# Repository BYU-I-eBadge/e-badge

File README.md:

# eBadge

**eBadge** is a customizable, hackable electronics badge designed for students to explore, build, and learn throughout their academic journey. It’s more than just a badge—it's a personal electronics lab, wearable project canvas, and long-term learning tool.

## Features

- Custom PCB with microcontroller 
- Modular peripherals: LEDs, sensors, buttons, displays, etc.
- Fully programmable with open-source firmware
- Designed for learning — from blinking LEDs to building full apps
- Battery-powered & portable — perfect for hacking on the go

## What’s in This Repo?

```bash
e-badge/
├── docs/           # Project documentation, setup guides, and images
├── hardware/       # Schematics, PCB layouts, BOMs, and 3D models
├── firmware/       # Embedded code for the badge's microcontroller
├── software/       # Host-side apps, test tools, or configurators
├── assets/         # Logos, badge graphics, and artwork
├── test/           # Scripts for testing hardware and firmware
├── LICENSE-CODE
├── LICENSE-HARDWARE
├── LICENSE-DOCS
├── README.md
└── .gitignore
```
## License

- **Hardware** – [CERN-OHL-S v2.0](./LICENSE-HARDWARE)
- **Firmware/Code** – [MIT License](./LICENSE-CODE)
- **Docs & Assets** – [CC BY-SA 4.0](./LICENSE-DOCS)

## Contributors

- Nathan Jack (jackn@byui.edu)
- Lynn Watson (lynn@lswatson.com)
- Jason Allred (allredjas@byui.edu)
- Richard Grimmett (grimmettr@byui.edu)
- Carl Gibbons (gibbonsc@byui.edu)
- Craig Lindstrom (lindstromc@byui.edu)
- Gary Godderidge (godderidgeg@byui.edu)
- Matt Manley (manleym@byui.edu)

# TODO (Senior project, delete when done)
- Fix screen connector
	- Use LCSC part C11086

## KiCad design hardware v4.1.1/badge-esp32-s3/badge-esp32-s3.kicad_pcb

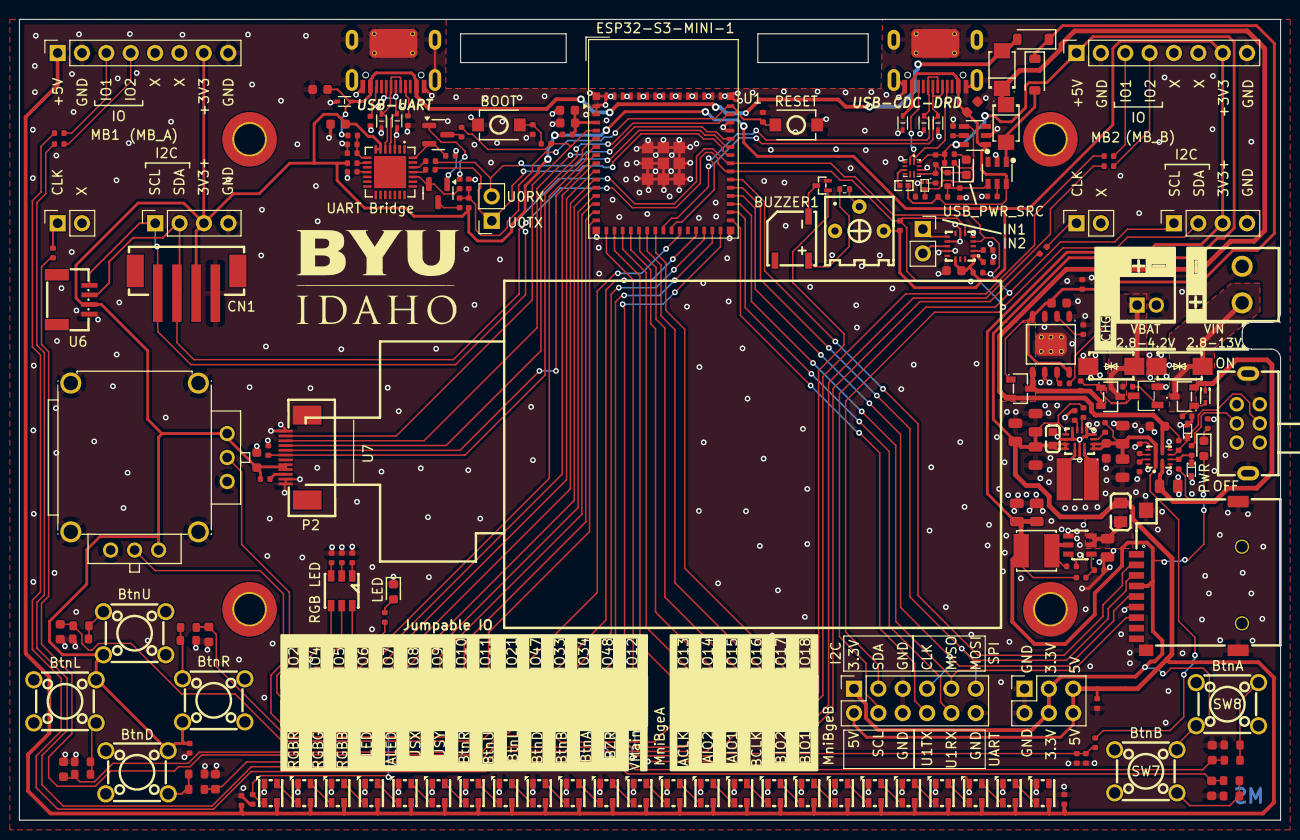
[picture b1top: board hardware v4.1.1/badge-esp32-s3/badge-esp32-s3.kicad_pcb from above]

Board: 2 copper layers, 131.5 x 83.5 mm, 215 parts (0 on the bottom side), 167 nets.

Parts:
AL1, AL2, AL3, AL4, AL5, AL6, AL7, AL8, AL9, AL10, AL11, AL12, AL13, AL14, AL15, AL16, AL17, AL18, AL19, AL20, AL21, AL22, AL23, AL24: SK6805MICRO-J; LED-SMD_4P-SK6805MICRO-J
BUZZER1: MLT-5020; BUZ-SMD_L5.0-W5.5-P4.60
C1, C5, C6, C7, C12, C24, C39: 10uF; C_0603
C2, C14: 100nF; C_0603
C3, C4, C10, C11, C25, C34, C35, C36, C41, C44: 100nF; C_0402
C8, C9, C15, C16, C32, C33: 1uF; C_0402
C18, C19, C20, C21, C22, C23: 1uF; C_0603
C26: 4.7uF; C_0603
C28, C29, C30, C31, C38, C40: 22uF; C_0805
C37: TMK107BBJ106MA-T; C0603
C42, C43, C45: 10uF; C_0805
CN1: B4B-PH-SM4-TB (LF)(SN); CONN-SMD_B4B-PH-SM4-TB-LF-SN
Card1: TF PUSH; TF-SMD_TF-PUSH
D1, D14, D19: Red; D_0603
D2, D3, D4, D6, D7, D8: LESD5D5.0CT1G; SOD-523_L1.2-W0.8-LS1.6-BI
D5, D16: B0520W; D_SOD-123
D9: SMAJ5.0CA_C116601; SMA_L4.3-W2.7-LS5.1-BI
D10: B5819WT; D_SOD-523
D11: MM5Z9V1T1G; SOD-523_L1.2-W0.8-LS1.6-RD-1
D12: Green; D_0805
D13: SMAJ13CA; SMA_L4.3-W2.7-LS5.1-BI
D15, D20: MM5Z5V1T1G; SOD-523F_L1.2-W0.8-LS1.7-RD
D17, D18: SS32F_C719168; SMAF_L3.5-W2.6-LS4.7-RD
H1, H2, H3, H4: MountingHole; MountingHole_3.2mm_M3_ISO7380_Pad_TopBottom
J1, J2: Connector, USB-TYPE-C-16P; TYPE-C-SMD_HX-TYPE-C-16PIN
J3, J9: Conn_02x06_Odd_Even; PinSocket_2x06_P2.54mm_Vertical
J4: Conn_02x15_Odd_Even; PinSocket_2x15_P2.54mm_Vertical
J5, J12, J14, J15: Conn_01x02_Socket; PinSocket_1x02_P2.54mm_Vertical
J6, J13: Conn_01x04_Socket; PinSocket_1x04_P2.54mm_Vertical
J7, J8: Conn_01x08_Socket; PinSocket_1x08_P2.54mm_Vertical
J11: Conn_02x03_Odd_Even; PinSocket_2x03_P2.54mm_Vertical
L1: ANR4030T3R9M; IND-SMD_L4.0-W4.0
L2: MPZ2012S101AT000; L0805
L4: FTC404020S1R5MGCA; IND-SMD_L4.1-W4.1_SPM40XX
LED1: RS-3535MWAM; LED-ARRAY-SMD_L3.7-W3.5-P1.10-TL
MB1, MB2: MiniBadge_Full; MiniBadge_Full_NoEdges
P1: PH-2A_C2319; CONN-TH_2P-P2.00_PH-2A_C2319
P2: FPC 0.5MM 12P Pull type H2.0mm Pick up; FPC-SMD_12P-L11.5-W5.4-P0.50
P3: WJ124-3.81-2P; CONN-TH_2P-P3.81_KF124-3.81-2P
Q1, Q2: SS8050 200-350; Q_SOT-23
Q3: AP1606; DFN-3L_L1.0-W0.6-P0.65-BR
Q5: DTC114E; DTC114EE
Q7, Q8, Q9: AO3415_C54938718; SOT-23-3_L2.9-W1.3-P1.90-LS2.4-BR
Q10: DMN3150L-7; SOT-23-3_L2.9-W1.6-P1.90-LS2.8-BR-CW
R1, R11, R12, R64: 0Ω; R_0402
R2: 3362P-1-501_C48997906; RES-ADJ-TH_3362P
R3, R4: 5.1kΩ; R_0402
R5: 910k; R0402
R6, R10, R13, R14, R17, R44, R46, R48, R66, R68, R69, R70: 10kΩ; R_0402
R7: 22kΩ; R_0402
R8: 47kΩ; R_0402
R9, R25: 1kΩ; R_0402
R15, R16, R55: 470Ω; R_0402
R18, R20, R40, R47, R49, R50, R51, R52: 100Ω; R_0402
R19: 24kΩ; R_0402
R21, R24: 47Ω; R_0402
R22, R54: 300Ω; R_0402
R23: YF16-FL7.2-B5KA(45-10)-R-A28; JOYTICK-TH_YF16-DFL7.2-B5KO-45-10-B5KO-55--RG-A22
R26: 2.2kΩ; R_0402
R27, R28, R29, R30, R31, R32, R33, R34, R35, R36, R37, R38: 10kΩ; R_0603
R39, R53, R56, R60, R62: 100kΩ; R_0402
R41: 150kΩ; R_0402
R42: 27Ω; R_0402_1005Metric
R43, R45: 4.7kΩ; R_0402
R58, R61: 3.3kΩ; R_0402
R59, R71: 1MΩ; R_0402
R63: 39kΩ; R_0402
R65: 12kΩ; R_0402
R67: 68kΩ; R_0402
SW1, SW2: TS-1088-AR02016; SW-SMD_L3.9-W3.0-P4.45
SW4, SW5, SW6, SW7, SW8, SW9: TS665CJ; SW-TH_4P-L6.0-W6.0-P4.50-LS6.5
SW10: SK22D02G5; SW-TH_SK22D02G5
U1: ESP32-S3-MINI-1-N4R2; ESP32-S2-MINI-1
U2: TPS630701RNMR; VQFN-HR-15_L3.0-W2.5-P0.50-BL_TPS63070RNMR
U3: CP2102N-A02-GQFN28R; QFN-28_L5.0-W5.0-P0.50-TL-EP3.3
U4: TP4056; ESOP-8_L4.9-W3.9-P1.27-LS6.0-BL-EP
U5: TPS2121RUXR; VQFN-HR-12_L2.5-W2.0-P0.50-BL
U6: ZX-SH1.0-4PWT; CONN-SMD_4P-P1.00_MEGASTAR_ZX-SH1.0-4PWT
U7: HS20HS072RX-fpc; OLED-SMD_HS20HS072RX-pins_removed
U8: TUSB321AIRWBR; X2QFN-12_L1.6-W1.6-P0.40-BL
U9: AP63203WU-7; TSOT-26_L2.9-W1.6-P0.95-LS2.8-BL
U11, U12: SY6288F1ABC; SOT-23-6_L2.9-W1.6-P0.95-LS2.8-BL
U18: MMA8452QR1_C11360; QFN-16_L3.0-W3.0-P0.50-TL_MMA8452QR1

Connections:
+3.3V: C7.1, C10.1, C14.1, C16.1, C26.2, C28.1, C29.1, CN1.3, Card1.4 (VDD), D1.2, J3.1, J6.3, J7.7, J8.7, J11.3, J11.4, J13.3, L1.2, P2.8 (IOVCC), P2.9 (VCC), R1.2, R2.3, R9.2, R17.1, R18.1, R23.3, R23.4, R43.1, R45.1, R64.1, SW4.2 (B), SW5.2 (B), SW6.2 (B), SW7.2 (B), SW8.2 (B), SW9.2 (B), U3.6 (VDD), U3.7 (VREGIN), U6.3, U18.1 (VDDIO), U18.14 (VDD)
/5V_stable: AL1.4 (VDD), AL2.4 (VDD), AL3.4 (VDD), AL4.4 (VDD), AL5.4 (VDD), AL6.4 (VDD), AL7.4 (VDD), AL8.4 (VDD), AL9.4 (VDD), AL10.4 (VDD), AL11.4 (VDD), AL12.4 (VDD), AL13.4 (VDD), AL14.4 (VDD), AL15.4 (VDD), AL16.4 (VDD), AL17.4 (VDD), AL18.4 (VDD), AL19.4 (VDD), AL20.4 (VDD), AL21.4 (VDD), AL22.4 (VDD), AL23.4 (VDD), AL24.4 (VDD), C15.1, C30.1, C31.1, C32.1, C33.1, C37.2, C40.1, J3.2, J7.1, J8.1, J11.5, J11.6, L2.1, R6.1, R53.1, R58.1, R69.1, U2.5 (FB), U2.7 (VOUT), U2.8 (VOUT), U8.12 (VDD), U12.6 (IN)
/AButtonMid: C22.1, J4.26, R36.2
/AddrLedMid: AL1.3 (DIN), J4.10, R68.1
/BButtonMid: C21.1, J4.24, R34.2
/BatteryVoltage: C34.1, J4.30, R41.2, R44.1
/BuzzerMid: J4.28, Q5.1 (B)
/DownButtonMid: C23.1, J4.22, R38.2
/ESP USB/CC1: J2.A5 (CC1), U8.1 (CC1)
/ESP USB/CC2: J2.B5 (CC2), U8.2 (CC2)
/ESP USB/USB_ID: D10.1, D19.1, R6.2, R66.1, U8.9 (ID)
/ESP USB/USB_SINK_EN: C3.1, D10.2, R70.2, U11.4 (EN/ENB)
/ESP USB/USB_SOURCE_EN: C4.1, Q3.3 (D), R69.2, U12.4 (EN/ENB)
/ESP USB/VBUS: C6.1, D8.2, J2.A9B4 (VBUS), J2.B9A4 (VBUS), R5.1, R70.1, U11.6 (IN), U12.1 (OUT)
/ESP_EN: C9.1, C36.2, R15.2, R17.2, SW2.2, U1.45 (EN)
/ESP_USB+: D6.2, J2.A6 (D+), J2.B6 (D+), U1.24 (USB_D+)
/ESP_USB-: D7.2, J2.A7 (D-), J2.B7 (D-), U1.23 (USB_D-)
/GPIO0: P2.2 (CS), R16.2, R55.2, U1.4 (IO0)
/GPIO1: P2.6 (RST), R39.1, U1.5 (IO1)
/GPIO2: J4.1, U1.6 (IO2)
/GPIO3: P2.5 (SDA), U1.7 (IO3)
/GPIO4: J4.3, U1.8 (IO4)
/GPIO5: J4.5, U1.9 (IO5)
/GPIO6: J4.7, U1.10 (IO6)
/GPIO7: J4.9, U1.11 (IO7)
/GPIO8: J4.11, U1.12 (IO8)
/GPIO9: J4.13, U1.13 (IO9)
/GPIO10: J4.15, U1.14 (IO10)
/GPIO11: J4.17, U1.15 (IO11)
/GPIO12: J4.29, U1.16 (IO12)
/GPIO13: J9.1, U1.17 (IO13)
/GPIO14: J9.3, U1.18 (IO14)
/GPIO15: J9.5, U1.19 (IO15)
/GPIO16: J9.7, U1.20 (IO16)
/GPIO17: J9.9, U1.21 (IO17)
/GPIO18: J9.11, U1.22 (IO18)
/GPIO21: J4.19, U1.25 (IO21)
/GPIO33: J4.23, U1.28 (IO33)
/GPIO34: J4.25, U1.29 (IO34)
/GPIO35: J3.8, U1.31 (IO35)
/GPIO36: J3.10, U1.32 (IO36)
/GPIO37: Card1.7 (DAT0), J3.9, U1.33 (IO37)
/GPIO38: Card1.5 (CLX), J3.7, U1.34 (IO38)
/GPIO39: Card1.3 (CMD), J3.11, U1.35 (IO39)
/GPIO40: Card1.2 (CD/DAT3), U1.36 (IO40)
/GPIO41: CN1.2, J3.3, J6.2, J13.2, R45.2, U1.37 (IO41), U6.2, U18.6 (SDA)
/GPIO42: CN1.1, J3.4, J6.1, J13.1, R43.2, U1.38 (IO42), U6.1, U18.4 (SCL)
/GPIO45: P2.3 (RS), U1.41 (IO45)
/GPIO46: P2.4 (SCL), U1.44 (IO46)
/GPIO47: J4.21, U1.27 (IO47)
/GPIO48: J4.27, U1.30 (IO48)
/JoystickXMid: J4.12, R23.2
/JoystickYMid: J4.14, R23.5
/LEDSingleMid: J4.8, R22.1
/LEDs/AL8_OUT: AL8.1 (DOUT), AL9.3 (DIN)
/LEDs/AL16_OUT: AL16.1 (DOUT), AL17.3 (DIN)
/LeftButtonMid: C18.1, J4.20, R28.2
/Onboard Peripheral/Accelormeter/INT 1 (output to MCU, NN): J15.2, U18.11 (INT1)
/Onboard Peripheral/Accelormeter/INT 2 (output to MCU, NN): J15.1, U18.9 (INT2)
/Power Input Managment/BATT_RAW: D9.2, P1.1, Q7.3 (D), R62.1
/Power Input Managment/OV1_EN_N: D20.1 (K), R71.2, SW10.2, U5.5 (OV1)
/Power Input Managment/OV2_EN_N: R67.2, SW10.5
/Power Input Managment/VIN: C42.1, D11.1 (K), Q8.2 (S), R59.1, U5.2 (IN2)
/Power Input Managment/VIN_RAW: D13.2, P3.1, Q8.3 (D)
/RGBBlueMid: J4.6, LED1.6 (+)
/RGBGreenMid: J4.4, LED1.5 (+)
/RGBRedMid: J4.2, LED1.4 (+)
/RightButtonMid: C20.1, J4.16, R32.2
/U0RX: J14.2, R11.2, U1.40 (RXD0)
/U0TX: J14.1, R12.2, U1.39 (TXD0)
/UART Interface/USB_DN: D3.2, J1.A7 (D-), J1.B7 (D-), U3.5 (D-)
/UART Interface/USB_DP: D2.2, J1.A6 (D+), J1.B6 (D+), U3.4 (D+)
/USB_HC: C24.1, D17.1 (K), D18.1 (K), Q9.2 (S), R71.1, U5.7 (IN1)
/USB_LC: C12.1, D5.1, D12.2, D16.1, Q9.1 (G), R56.1, U4.4 (VCC), U4.8 (CE)
/UpButtonMid: C19.1, J4.18, R30.2
/VBATT: Q7.2 (S), Q9.3 (D), R60.1, U4.5 (BAT)
/VBUS: C5.1, D4.2, D5.2, D17.2 (A), J1.A9B4 (VBUS), J1.B9A4 (VBUS), R7.1
/Voltage Management/SW: C44.2, L1.1, U9.5 (SW)
/Voltage Management/VIN: C38.1, L2.2, U9.2 (EN), U9.3 (VIN)
/minibadge/MB1CLK: J9.2, R49.2
/minibadge/MB1IO1: J9.6, R40.1
/minibadge/MB1IO2: J9.4, R47.1
/minibadge/MB2CLK: J9.8, R52.2
/minibadge/MB2IO1: J9.12, R50.1
/minibadge/MB2IO2: J9.10, R51.1
GND: AL1.2 (VSS), AL2.2 (VSS), AL3.2 (VSS), AL4.2 (VSS), AL5.2 (VSS), AL6.2 (VSS), AL7.2 (VSS), AL8.2 (VSS), AL9.2 (VSS), AL10.2 (VSS), AL11.2 (VSS), AL12.2 (VSS), AL13.2 (VSS), AL14.2 (VSS), AL15.2 (VSS), AL16.2 (VSS), AL17.2 (VSS), AL18.2 (VSS), AL19.2 (VSS), AL20.2 (VSS), AL21.2 (VSS), AL22.2 (VSS), AL23.2 (VSS), AL24.2 (VSS), C1.2, C2.2, C3.2, C4.2, C5.2, C6.2, C7.2, C8.2, C9.2, C10.2, C11.2, C12.2, C14.2, C15.2, C16.2, C18.2, C19.2, C20.2, C21.2, C22.2, C23.2, C24.2, C25.2, C26.1, C28.2, C29.2, C30.2, C31.2, C32.2, C33.2, C34.2, C35.1, C36.1, C37.1, C38.2, C39.2, C40.2, C41.2, C42.2, C43.2, C45.2, CN1.4, Card1.6 (VSS), Card1.10, Card1.11, Card1.12, Card1.13, D2.1, D3.1, D4.1, D6.1, D7.1, D8.1, D9.1, D13.1, D14.1, D15.2 (A), D20.2 (A), J1.A12B1 (GND), J1.B12A1 (GND), J1.S1 (SHIELD), J2.A12B1 (GND), J2.B12A1 (GND), J2.S1 (SHIELD), J3.5, J3.6, J3.12, J6.4, J7.2, J7.8, J8.2, J8.8, J11.1, J11.2, J13.4, P1.2, P2.1 (GND), P2.11 (K), P2.12 (GND), P3.2, Q3.2 (S), Q5.2 (E), Q10.3 (S), R3.2, R4.2, R8.2, R10.2, R19.2, R20.2, R21.2, R23.1, R23.6, R23.7 (shell), R23.8 (shell), R23.9 (shell), R23.10 (shell), R24.2, R26.2, R27.2, R29.2, R31.2, R33.2, R35.2, R37.2, R39.2, R44.2, R48.2, R54.1, R56.2, R61.2, R63.2, R65.2, R68.2, SW1.1, SW2.1, SW10.3, SW10.4, SW10.7, SW10.8, U1.1 (GND), U1.2 (GND), U1.42 (GND), U1.43 (GND), U1.46 (GND), U1.47 (GND), U1.48 (GND), U1.49 (GND), U1.50 (GND), U1.51 (GND), U1.52 (GND), U1.53 (GND), U1.54 (GND), U1.55 (GND), U1.56 (GND), U1.57 (GND), U1.58 (GND), U1.59 (GND), U1.60 (GND), U1.61 (GND), U1.62 (GND), U1.63 (GND), U1.64 (GND), U1.65 (GND), U2.1 (PS/SYNC), U2.4 (GND), U2.6 (FB2), U2.10 (PGND), U2.15 (VSEL), U3.3 (GND), U4.1 (TEMP), U4.3 (GND), U4.6 (STDBY#), U4.9 (EP), U5.3 (CP2), U5.6 (PR1), U5.9 (ST), U5.12 (GND), U6.4, U8.3 (CURRENT_MODE), U8.10 (GND), U9.4 (GND), U11.2 (GND), U12.2 (GND), U18.5 (GND), U18.7 (SA0), U18.10 (GND), U18.12 (GND)
unnamed: AL1.1 (DOUT), AL2.3 (DIN)
unnamed: AL2.1 (DOUT), AL3.3 (DIN)
unnamed: AL3.1 (DOUT), AL4.3 (DIN)
unnamed: AL4.1 (DOUT), AL5.3 (DIN)
unnamed: AL5.1 (DOUT), AL6.3 (DIN)
unnamed: AL6.1 (DOUT), AL7.3 (DIN)
unnamed: AL7.1 (DOUT), AL8.3 (DIN)
unnamed: AL9.1 (DOUT), AL10.3 (DIN)
unnamed: AL10.1 (DOUT), AL11.3 (DIN)
unnamed: AL11.1 (DOUT), AL12.3 (DIN)
unnamed: AL12.1 (DOUT), AL13.3 (DIN)
unnamed: AL13.1 (DOUT), AL14.3 (DIN)
unnamed: AL14.1 (DOUT), AL15.3 (DIN)
unnamed: AL15.1 (DOUT), AL16.3 (DIN)
unnamed: AL17.1 (DOUT), AL18.3 (DIN)
unnamed: AL18.1 (DOUT), AL19.3 (DIN)
unnamed: AL19.1 (DOUT), AL20.3 (DIN)
unnamed: AL20.1 (DOUT), AL21.3 (DIN)
unnamed: AL21.1 (DOUT), AL22.3 (DIN)
unnamed: AL22.1 (DOUT), AL23.3 (DIN)
unnamed: AL23.1 (DOUT), AL24.3 (DIN)
unnamed: BUZZER1.1 (+), R42.2
unnamed: BUZZER1.2 (-), Q5.3 (C)
unnamed: C35.2, R55.1, SW1.2
unnamed: D1.1, R54.2
unnamed: D11.2 (A), Q8.1 (G), R48.1
unnamed: D12.1, R25.1
unnamed: D14.2, R22.2
unnamed: D15.1 (K), R59.2, R67.1, U5.4 (OV2)
unnamed: D16.2, D18.2 (A), U11.1 (OUT)
unnamed: D19.2, R58.2
unnamed: J1.A5 (CC1), R3.1
unnamed: J1.B5 (CC2), R4.1
unnamed: J5.1, R49.1
unnamed: J7.3, R40.2
unnamed: J7.4, R47.2
unnamed: J8.3, R50.2
unnamed: J8.4, R51.2
unnamed: J12.1, R52.1
unnamed: LED1.1 (-), R21.1
unnamed: LED1.2 (-), R24.1
unnamed: LED1.3 (-), R20.1
unnamed: P2.10 (A), R18.2
unnamed: Q1.1 (B), R13.2
unnamed: Q1.3 (C), R15.1
unnamed: Q1.2 (E), R14.1, U3.24 (RTS)
unnamed: Q2.1 (B), R14.2
unnamed: Q2.3 (C), R16.1
unnamed: Q2.2 (E), R13.1, U3.28 (DTR)
unnamed: Q3.1 (G), R66.2
unnamed: Q7.1 (G), Q10.2 (D), R60.2
unnamed: Q10.1 (G), R62.2
unnamed: R2.2, R42.1
unnamed: R27.1, R28.1, SW4.4 (D)
unnamed: R29.1, R30.1, SW5.4 (D)
unnamed: R31.1, R32.1, SW6.4 (D)
unnamed: R33.1, R34.1, SW7.4 (D)
unnamed: R35.1, R36.1, SW8.3 (C)
unnamed: R37.1, R38.1, SW9.4 (D)
unnamed: C1.1, C2.1, R1.1, U1.3 (3V3)
unnamed: R46.2, U2.14 (EN)
unnamed: L4.1, U2.11 (L1)
unnamed: L4.2, U2.9 (L2)
unnamed: R53.2, U2.2 (PG)
unnamed: C25.1, U2.3 (VAUX)
unnamed: R9.1, U3.9 (RSTb)
unnamed: R12.1, U3.25 (RXD)
unnamed: R10.1, U3.11 (SUSPENDb)
unnamed: R11.1, U3.26 (TXD)
unnamed: C8.1, R7.2, R8.1, U3.8 (VBUS)
unnamed: R25.2, U4.7 (CHRG#)
unnamed: R26.1, U4.2 (PROG)
unnamed: R63.1, U5.10 (ILM)
unnamed: C41.1, U5.11 (SS)
unnamed: R5.2, U8.5 (VBUS_DET)
unnamed: C44.1, U9.6 (BST)
unnamed: R19.1, R64.2, U9.1 (FB)
unnamed: R61.1, U11.5 (ISET)
unnamed: R65.1, U12.5 (ISET)
unnamed: C11.1, U18.2 (BYP)
PWR_RAW: C39.1, C43.1, C45.1, R41.1, R46.1, U2.12 (VIN), U2.13 (VIN), U5.1 (OUT), U5.8 (OUT)

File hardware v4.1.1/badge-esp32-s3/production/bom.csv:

Designator,Footprint,Quantity,Value,LCSC Part #
"AL1, AL10, AL11, AL12, AL13, AL14, AL15, AL16, AL17, AL18, AL19, AL2, AL20, AL21, AL22, AL23, AL24, AL3, AL4, AL5, AL6, AL7, AL8, AL9",LED-SMD_4P-SK6805MICRO-J,24,SK6805MICRO-J,C2909056
BUZZER1,BUZ-SMD_L5.0-W5.5-P4.60,1,MLT-5020,C94598
"C1, C12, C24, C39, C5, C6, C7",C_0603,7,10uF,C96446
"C10, C11, C25, C3, C35, C36, C4",C_0402,7,100nF,C1525
"C14, C2",C_0603,2,100nF,C14663
"C15, C16, C32, C33, C8, C9",C_0402,6,1uF,C52923
"C18, C19, C20, C21, C22, C23",C_0603,6,1uF,C15849
C26,C_0603,1,4.7uF,C19666
"C28, C29, C30, C31, C38, C40",C_0805,6,22uF,C296720
"C34, C41, C44",C_0402,3,100nF,C307331
C37,C0603,1,TMK107BBJ106MA-T,C386081
"C42, C43, C45",C_0805,3,10uF,C440198
CARD1,TF-SMD_TF-PUSH,1,TF PUSH,C393941
CN1,CONN-SMD_B4B-PH-SM4-TB-LF-SN,1,B4B-PH-SM4-TB (LF)(SN),C160354
"D1, D14, D19",D_0603,3,Red,C2286
D10,D_SOD-523,1,B5819WT,C7502714
D11,SOD-523_L1.2-W0.8-LS1.6-RD-1,1,MM5Z9V1T1G,C242268
D12,D_0805,1,Green,C2297
D13,SMA_L4.3-W2.7-LS5.1-BI,1,SMAJ13CA,C19077534
"D15, D20",SOD-523F_L1.2-W0.8-LS1.7-RD,2,MM5Z5V1T1G,C146754
"D16, D5",D_SOD-123,2,B0520W,C7502707
"D17, D18",SMAF_L3.5-W2.6-LS4.7-RD,2,SS32F_C719168,C719168
"D2, D3, D4, D6, D7, D8",SOD-523_L1.2-W0.8-LS1.6-BI,6,LESD5D5.0CT1G,C5199850
D9,SMA_L4.3-W2.7-LS5.1-BI,1,SMAJ5.0CA_C116601,C116601
"J1, J2",TYPE-C-SMD_HX-TYPE-C-16PIN,2,"Connector, USB-TYPE-C-16P",C2927039
J11,PinSocket_2x03_P2.54mm_Vertical,1,Conn_02x03_Odd_Even,C541853
"J12, J14, J15, J5",PinSocket_1x02_P2.54mm_Vertical,4,Conn_01x02_Socket,C7499322
"J13, J6",PinSocket_1x04_P2.54mm_Vertical,2,Conn_01x04_Socket,C2718488
"J3, J9",PinSocket_2x06_P2.54mm_Vertical,2,Conn_02x06_Odd_Even,C5307342
J4,PinSocket_2x15_P2.54mm_Vertical,1,Conn_02x15_Odd_Even,C7499350
"J7, J8",PinSocket_1x08_P2.54mm_Vertical,2,Conn_01x08_Socket,C42385698
L1,IND-SMD_L4.0-W4.0,1,ANR4030T3R9M,C6808101
L2,L0805,1,MPZ2012S101AT000,C15957
L4,IND-SMD_L4.1-W4.1_SPM40XX,1,FTC404020S1R5MGCA,C39676069
LED1,LED-ARRAY-SMD_L3.7-W3.5-P1.10-TL,1,RS-3535MWAM,C842778
P1,CONN-TH_2P-P2.00_PH-2A_C2319,1,PH-2A_C2319,C2319
P2,FPC-SMD_12P-L11.5-W5.4-P0.50,1,FPC 0.5MM 12P Pull type H2.0mm Pick up,C11086
P3,CONN-TH_2P-P3.81_KF124-3.81-2P,1,WJ124-3.81-2P,C69811
"Q1, Q2",Q_SOT-23,2,SS8050 200-350,C2150
Q10,SOT-23-3_L2.9-W1.6-P1.90-LS2.8-BR-CW,1,DMN3150L-7,C156268
Q3,DFN-3L_L1.0-W0.6-P0.65-BR,1,AP1606,C2849580
Q5,DTC114EE,1,DTC114E,C94400
"Q7, Q8, Q9",SOT-23-3_L2.9-W1.3-P1.90-LS2.4-BR,3,AO3415_C54938718,C54938718
"R1, R11, R12, R64",R_0402,4,0Ω,C17168
"R10, R13, R14, R17, R44, R46, R48, R6, R66, R68, R69, R70",R_0402,12,10kΩ,C25744
"R15, R16, R55",R_0402,3,470Ω,C25117
"R18, R20, R40, R47, R49, R50, R51, R52",R_0402,8,100Ω,C25076
R2,RES-ADJ-TH_3362P,1,3362P-1-501_C48997906,C48997906
"R21, R24",R_0402,2,47Ω,C25118
"R22, R54",R_0402,2,300Ω,C25102
R23,JOYTICK-TH_YF16-DFL7.2-B5KO-45-10-B5KO-55--RG-A22,1,YF16-FL7.2-B5KA(45-10)-R-A28,C37323739
"R25, R9",R_0402,2,1kΩ,C11702
R26,R_0402,1,2.2kΩ,C25879
"R27, R28, R29, R30, R31, R32, R33, R34, R35, R36, R37, R38",R_0603,12,10kΩ,C25804
"R3, R4",R_0402,2,5.1kΩ,C25905
"R39, R53, R56, R60, R62",R_0402,5,100kΩ,C25741
R41,R_0402,1,150kΩ,C25755
R42,0402,1,27Ω,
"R43, R45",R_0402,2,4.7kΩ,C25900
R5,R0402,1,910k,C2909391
"R58, R61",R_0402,2,3.3kΩ,C25890
"R59, R71",R_0402,2,1MΩ,C26083
R63,R_0402,1,39kΩ,C25783
R65,R_0402,1,12kΩ,C25752
R67,R_0402,1,68kΩ,C36871
R7,R_0402,1,22kΩ,C25768
R8,R_0402,1,47kΩ,C25792
"SW1, SW2",SW-SMD_L3.9-W3.0-P4.45,2,TS-1088-AR02016,C720477
SW10,SW-TH_SK22D02G5,1,SK22D02G5,C22435630
"SW4, SW5, SW6, SW7, SW8, SW9",SW-TH_4P-L6.0-W6.0-P4.50-LS6.5,6,TS665CJ,C393938
U1,ESP32-S2-MINI-1,1,ESP32-S3-MINI-1-N4R2,C3013941
"U11, U12",SOT-23-6_L2.9-W1.6-P0.95-LS2.8-BL,2,SY6288F1ABC,C2875458
U18,QFN-16_L3.0-W3.0-P0.50-TL_MMA8452QR1,1,MMA8452QR1_C11360,C11360
U2,VQFN-HR-15_L3.0-W2.5-P0.50-BL_TPS63070RNMR,1,TPS630701RNMR,C2876599
U3,QFN-28_L5.0-W5.0-P0.50-TL-EP3.3,1,CP2102N-A02-GQFN28R,C964632
U4,ESOP-8_L4.9-W3.9-P1.27-LS6.0-BL-EP,1,TP4056,C16581
U5,VQFN-HR-12_L2.5-W2.0-P0.50-BL,1,TPS2121RUXR,C485916
U6,CONN-SMD_4P-P1.00_MEGASTAR_ZX-SH1.0-4PWT,1,ZX-SH1.0-4PWT,C7430446
U8,X2QFN-12_L1.6-W1.6-P0.40-BL,1,TUSB321AIRWBR,C2674046
U9,TSOT-26_L2.9-W1.6-P0.95-LS2.8-BL,1,AP63203WU-7,C780769

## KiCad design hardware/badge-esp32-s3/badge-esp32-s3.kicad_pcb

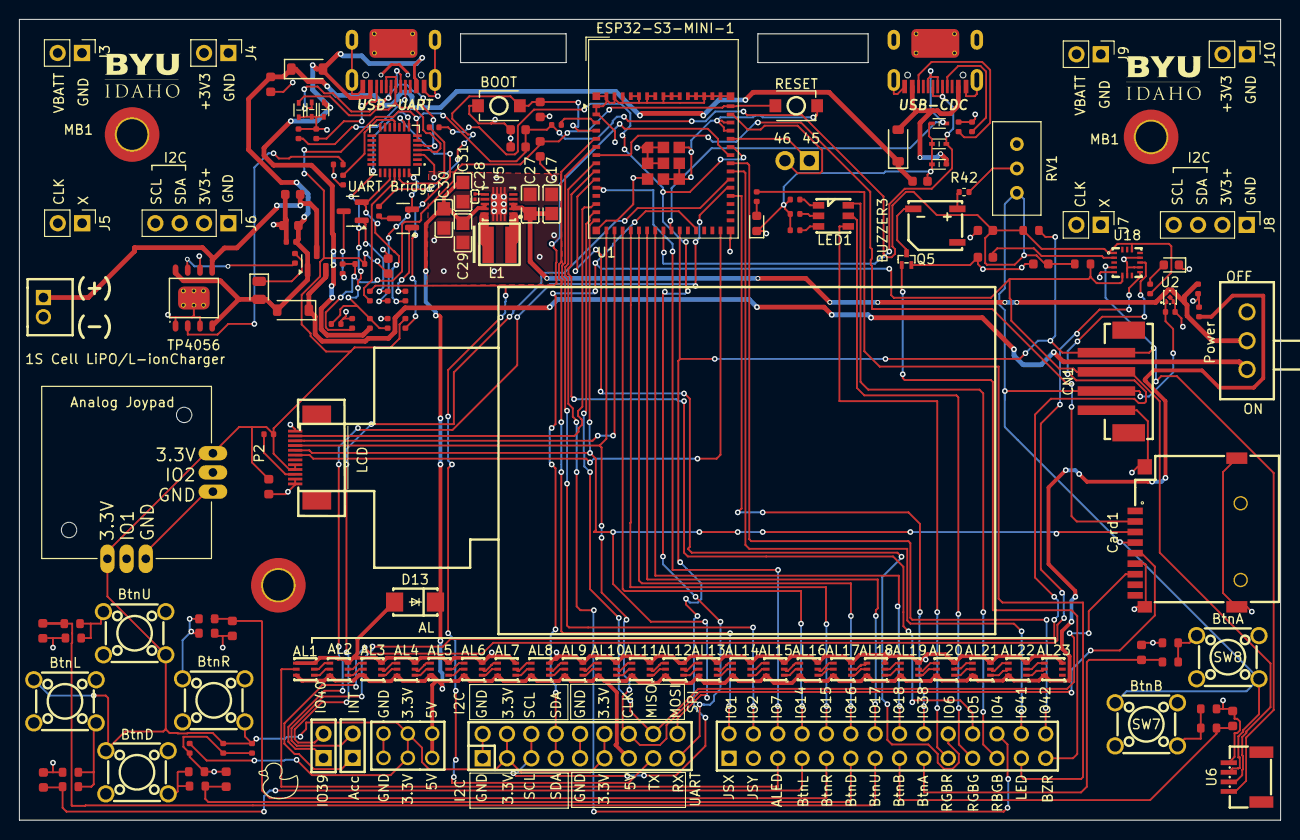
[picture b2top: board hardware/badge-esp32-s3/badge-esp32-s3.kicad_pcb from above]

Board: 2 copper layers, 131.5 x 83.5 mm, 157 parts (0 on the bottom side), 140 nets.

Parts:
AL1, AL2, AL3, AL4, AL5, AL6, AL7, AL8, AL9, AL10, AL11, AL12, AL13, AL14, AL15, AL16, AL17, AL18, AL19, AL20, AL21, AL22, AL23: LED-SMD_6P-L2.2-W2.2-TL-1
BUZZER3: MLT-5020; BUZ-SMD_L5.0-W5.5-P4.60
C1, C5, C6, C7, C12, C13: 10uF; C_0603
C2, C10, C11, C14, C24, C25: 100nF; C_0603
C3, C4, C8, C9, C15, C15#2, C16, C17: 1uF; C_0402
C17#2, C27: 10uF; C0805
C18, C19, C20, C21, C22, C23: 1uF; C_0603
C26: 4.7uF; C_0603
C28: 100nF; C0201
C29, C30, C31: 22uF; C0805
CN1: B4B-PH-SM4-TB (LF)(SN); CONN-SMD_B4B-PH-SM4-TB-LF-SN
CN2: HDR-TH_2P-P2.54-V-F
CN3: HDR-TH_2P-P2.54-V-F
Card1: TF PUSH; TF-SMD_TF-PUSH
D1, D10: Red; D_0603
D2, D3, D4, D6, D7, D8: LESD5D5.0CT1G; SOD-523_L1.2-W0.8-LS1.6-BI
D5, D9, D11: B0520W; D_SOD-123
D12: Green; D_0805
D13: SMAJ7.0A; SMA_L4.5-W2.6-LS5.1-RD
H2: HDR-TH_18P-P2.54-V-F-R2-C9-S2.54-1
J1, J2: Connector, USB-TYPE-C-16P; TYPE-C-SMD_HX-TYPE-C-16PIN
J3, J4, J5, J7, J9, J10: Conn_01x02_Socket; PinHeader_1x02_P2.54mm_Vertical
J6, J8: Conn_01x04_Socket; PinHeader_1x04_P2.54mm_Vertical
L1: 1uH; IND-SMD_L4.0-W4.0_XFL4020-102MEB
LCD: OLED-SMD_HS20HS072RX
LED1: RS-3535MWAM; LED-ARRAY-SMD_L3.7-W3.5-P1.10-TL
MB1, MB1#2: MiniBadge_Full; MiniBadge_Full_NoEdges
P1: PH-2A_C2319; CONN-TH_2P-P2.00_PH-2A_C2319
P2: FPC 0.5MM 12P Pull type H2.0mm Pick up; FPC-SMD_12P-L11.5-W5.4-P0.50
Power1: SK-12F04-G050; SW-TH_G-SWITCH_SK-12F04-G050
Q1, Q2: SS8050 200-350; Q_SOT-23
Q3: HL2301A; Q_SOT-23
Q5: DTC114E; SOT-523_L1.6-W0.8-P1.00-BR
R1, R11, R12, R15, R16: 0Ω; R_0402
R2, R3, R4, R5, R6, R19: 5.1kΩ; R_0402
R7: 22kΩ; R_0402
R8: 47kΩ; R_0402
R9, R25: 1kΩ; R_0402
R10, R13, R14, R17: 10kΩ; R_0402
R18, R20: 100Ω; R_0402
R21, R22: 47Ω; R_0402
R24: 100kΩ; R_0402
R26: 2.2kΩ; R_0402
R27, R28, R29, R30, R31, R32, R33, R34, R35, R36, R37, R38: 10kΩ; R_0603
R39, R40: 4.7kΩ; R_0603
R42: 27Ω; R_0402_1005Metric
RV1: 1000Ω; Potentiometer_Bourns_3296W_Vertical
S1: 2765; SW_2765
SW1, SW2: TS-1088-AR02016; SW-SMD_L3.9-W3.0-P4.45
SW4, SW5, SW6, SW7, SW8, SW9: TS665CJ; SW-TH_4P-L6.0-W6.0-P4.50-LS6.5
U1: ESP32-S3-MINI-1-N4R2; ESP32-S2-MINI-1
U2: NCP167BMX330TBG; XDFN-4_L1.0-W1.0-P0.65-BL-EP
U3: CP2102N-A02-GQFN28R; QFN-28_L5.0-W5.0-P0.50-TL-EP3.3
U4: TP4056; ESOP-8_L4.9-W3.9-P1.27-LS6.0-BL-EP
U5: TPS63061DSCR; WSON-10_L3.0-W3.0-P0.50-BL-EP-A
U6: ZX-SH1.0-4PWT; CONN-SMD_4P-P1.00_MEGASTAR_ZX-SH1.0-4PWT
U14: CONN-TH_HX-PM2.54-2X3P-ZC
U18: MMA8452QR1_C11360; QFN-16_L3.0-W3.0-P0.50-TL_MMA8452QR1
U19: FH2.54-09-02PZD; HDR-TH_2P-P2.54-V-M-5
U20: 2x14_female; HDR-TH_28P-P2.54-V-F-R2-C14-S2.54

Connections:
+3.3V: C1.1, C2.1, C4.1, C7.1, C14.1, C15#2.1, C16.1, C17.1, C24.2, C26.2, CN1.3, Card1.4 (VDD), H2.3, H2.4, H2.11, H2.12, P2.8 (IOVCC), P2.9 (VCC), R1.1, R2.1, R9.2, R17.1, R18.1, R39.1, R40.1, RV1.1, S1.X-, S1.Y-, SW4.1 (A), SW5.1 (A), SW6.1 (A), SW7.1 (A), SW8.1 (A), SW9.1 (A), U2.1 (OUT), U3.6 (VDD), U3.7 (VREGIN), U6.3, U14.2, U14.5, U18.1 (VDDIO), U18.14 (VDD)
+4V: C3.1, C17#2.2, C27.2, Power1.2, U2.3 (EN), U2.4 (IN), U5.2 (VIN), U5.3 (EN)
/5V_stable: AL1.3 (VDD), AL2.3 (VDD), AL3.3 (VDD), AL4.3 (VDD), AL5.3 (VDD), AL6.3 (VDD), AL7.3 (VDD), AL8.3 (VDD), AL9.3 (VDD), AL10.3 (VDD), AL11.3 (VDD), AL12.3 (VDD), AL13.3 (VDD), AL14.3 (VDD), AL15.3 (VDD), AL16.3 (VDD), AL17.3 (VDD), AL18.3 (VDD), AL19.3 (VDD), AL20.3 (VDD), AL21.3 (VDD), AL22.3 (VDD), AL23.3 (VDD), C15.1, C29.2, C30.2, C31.2, D13.1 (K), H2.13, U5.8 (FB), U5.9 (VOUT), U14.3, U14.4
/AButtonMid: C22.1, R36.2, U20.17
/AddrLedMid: AL1.2 (DI), U20.5
/BButtonMid: C21.1, R34.2, U20.15
/BuzzerMid: Q5.1 (B), U20.27
/Charging/VBATT: C13.1, P1.1, Q3.3 (D), U4.5 (BAT)
/DownButtonMid: C23.1, R38.2, U20.11
/ESP_EN: C9.1, C11.2, R15.2, R17.2, SW2.2, U1.45 (EN)
/ESP_USB+: D6.2, J2.A6 (D+), J2.B6 (D+), U1.24 (USB_D+)
/ESP_USB-: D7.2, J2.A7 (D-), J2.B7 (D-), U1.23 (USB_D-)
/GPIO0: C10.2, R16.2, SW1.2, U1.4 (IO0)
/GPIO1: U1.5 (IO1), U20.2
/GPIO2: U1.6 (IO2), U20.4
/GPIO3: Card1.2 (CD/DAT3), U1.7 (IO3)
/GPIO4: U1.8 (IO4), U20.24
/GPIO5: U1.9 (IO5), U20.22
/GPIO6: U1.10 (IO6), U20.20
/GPIO7: U1.11 (IO7), U20.6
/GPIO9: P2.2 (CS), U1.13 (IO9)
/GPIO10: Card1.7 (DAT0), H2.16, U1.14 (IO10)
/GPIO11: Card1.3 (CMD), H2.18, P2.5 (SDA), U1.15 (IO11)
/GPIO12: Card1.5 (CLX), H2.14, P2.4 (SCL), U1.16 (IO12)
/GPIO13: P2.3 (RS), U1.17 (IO13)
/GPIO14: U1.18 (IO14), U20.8
/GPIO15: U1.19 (IO15), U20.10
/GPIO16: U1.20 (IO16), U20.12
/GPIO17: U1.21 (IO17), U20.14
/GPIO18: U1.22 (IO18), U20.16
/GPIO21: CN1.1, H2.5, H2.6, R39.2, U1.25 (IO21), U6.1, U18.4 (SCL)
/GPIO38: U1.34 (IO38), U20.18
/GPIO39: CN3.1, U1.35 (IO39)
/GPIO40: CN3.2, U1.36 (IO40)
/GPIO41: U1.37 (IO41), U20.26
/GPIO42: U1.38 (IO42), U20.28
/GPIO45: U1.41 (IO45), U19.1
/GPIO46: U1.44 (IO46), U19.2
/GPIO47: CN1.2, H2.7, H2.8, R40.2, U1.27 (IO47), U6.2, U18.6 (SDA)
/GPIO48: P2.6 (RST), U1.30 (IO48)
/LEDSingleMid: R19.1, U20.25
/LEDs/BO_AL9: AL9.5 (BO), AL10.1 (BI)
/LEDs/BO_AL18: AL18.5 (BO), AL19.1 (BI)
/LEDs/DO_AL9: AL9.4 (DO), AL10.2 (DI)
/LEDs/DO_AL18: AL18.4 (DO), AL19.2 (DI)
/LeftButtonMid: C20.1, R32.2, U20.9
/Onboard Peripheral/Accelormeter/INT 1 (output to MCU, NN): CN2.2, U18.11 (INT1)
/Onboard Peripheral/Accelormeter/INT 2 (output to MCU, NN): CN2.1, U18.9 (INT2)
/RGBBlueMid: LED1.6 (+), U20.23
/RGBGreenMid: LED1.5 (+), U20.21
/RGBRedMid: LED1.4 (+), U20.19
/RightButtonMid: C18.1, R28.2, U20.7
/U0RX: H2.17, R11.2, U1.40 (RXD0)
/U0TX: H2.15, R12.2, U1.39 (TXD0)
/UART Interface/USB_DN: D3.2, J1.A7 (D-), J1.B7 (D-), U3.5 (D-)
/UART Interface/USB_DP: D2.2, J1.A6 (D+), J1.B6 (D+), U3.4 (D+)
/USB_5V: C5.1, C6.1, C12.1, D5.1, D9.1, D11.2, D12.2, Q3.1 (G), R24.2, U4.4 (VCC), U4.8 (CE)
/UpButtonMid: C19.1, R30.2, U20.13
/VBUS: D4.2, D5.2, J1.A9B4 (VBUS), J1.B9A4 (VBUS), R7.1
/VBUSB: D8.2, D9.2, J2.A9B4 (VBUS), J2.B9A4 (VBUS)
GND: AL1.1 (BI), AL1.6 (GND), AL2.6 (GND), AL3.6 (GND), AL4.6 (GND), AL5.6 (GND), AL6.6 (GND), AL7.6 (GND), AL8.6 (GND), AL9.6 (GND), AL10.6 (GND), AL11.6 (GND), AL12.6 (GND), AL13.6 (GND), AL14.6 (GND), AL15.6 (GND), AL16.6 (GND), AL17.6 (GND), AL18.6 (GND), AL19.6 (GND), AL20.6 (GND), AL21.6 (GND), AL22.6 (GND), AL23.6 (GND), C1.2, C2.2, C3.2, C4.2, C5.2, C6.2, C7.2, C8.2, C9.2, C10.1, C11.1, C12.2, C13.2, C14.2, C15.2, C15#2.2, C16.2, C17.2, C17#2.1, C18.2, C19.2, C20.2, C21.2, C22.2, C23.2, C24.1, C25.1, C26.1, C27.1, C28.1, C29.1, C30.1, C31.1, CN1.4, Card1.6 (VSS), Card1.10, Card1.11, Card1.12, Card1.13, D1.1, D2.1, D3.1, D4.1, D6.1, D7.1, D8.1, D10.1, D13.2 (A), H2.1, H2.2, H2.9, H2.10, J1.A12B1 (GND), J1.B12A1 (GND), J1.S1 (SHIELD), J2.A12B1 (GND), J2.B12A1 (GND), J2.S1 (SHIELD), P1.2, P2.1 (GND), P2.11 (K), P2.12 (GND), Power1.3, Q5.2 (E), R3.2, R4.2, R5.2, R6.2, R8.2, R10.2, R20.2, R21.2, R22.2, R24.1, R26.2, R27.2, R29.2, R31.2, R33.2, R35.2, R37.2, S1.X+, S1.Y+, SW1.1, SW2.1, U1.1 (GND), U1.2 (GND), U1.42 (GND), U1.43 (GND), U1.46 (GND), U1.47 (GND), U1.48 (GND), U1.49 (GND), U1.50 (GND), U1.51 (GND), U1.52 (GND), U1.53 (GND), U1.54 (GND), U1.55 (GND), U1.56 (GND), U1.57 (GND), U1.58 (GND), U1.59 (GND), U1.60 (GND), U1.61 (GND), U1.62 (GND), U1.63 (GND), U1.64 (GND), U1.65 (GND), U2.2 (GND), U2.5 (EPAD), U3.3 (GND), U4.1 (TEMP), U4.3 (GND), U4.6 (STDBY#), U4.9 (EP), U5.4 (PS/SYNC), U5.7 (GND), U5.11 (PGND), U6.4, U14.1, U14.6, U18.5 (GND), U18.7 (SA0), U18.10 (GND), U18.12 (GND)
unnamed: AL1.5 (BO), AL2.1 (BI)
unnamed: AL1.4 (DO), AL2.2 (DI)
unnamed: AL2.5 (BO), AL3.1 (BI)
unnamed: AL2.4 (DO), AL3.2 (DI)
unnamed: AL3.5 (BO), AL4.1 (BI)
unnamed: AL3.4 (DO), AL4.2 (DI)
unnamed: AL4.5 (BO), AL5.1 (BI)
unnamed: AL4.4 (DO), AL5.2 (DI)
unnamed: AL5.5 (BO), AL6.1 (BI)
unnamed: AL5.4 (DO), AL6.2 (DI)
unnamed: AL6.5 (BO), AL7.1 (BI)
unnamed: AL6.4 (DO), AL7.2 (DI)
unnamed: AL7.5 (BO), AL8.1 (BI)
unnamed: AL7.4 (DO), AL8.2 (DI)
unnamed: AL8.5 (BO), AL9.1 (BI)
unnamed: AL8.4 (DO), AL9.2 (DI)
unnamed: AL10.5 (BO), AL11.1 (BI)
unnamed: AL10.4 (DO), AL11.2 (DI)
unnamed: AL11.5 (BO), AL12.1 (BI)
unnamed: AL11.4 (DO), AL12.2 (DI)
unnamed: AL12.5 (BO), AL13.1 (BI)
unnamed: AL12.4 (DO), AL13.2 (DI)
unnamed: AL13.5 (BO), AL14.1 (BI)
unnamed: AL13.4 (DO), AL14.2 (DI)
unnamed: AL14.5 (BO), AL15.1 (BI)
unnamed: AL14.4 (DO), AL15.2 (DI)
unnamed: AL15.5 (BO), AL16.1 (BI)
unnamed: AL15.4 (DO), AL16.2 (DI)
unnamed: AL16.5 (BO), AL17.1 (BI)
unnamed: AL16.4 (DO), AL17.2 (DI)
unnamed: AL17.5 (BO), AL18.1 (BI)
unnamed: AL17.4 (DO), AL18.2 (DI)
unnamed: AL19.5 (BO), AL20.1 (BI)
unnamed: AL19.4 (DO), AL20.2 (DI)
unnamed: AL20.5 (BO), AL21.1 (BI)
unnamed: AL20.4 (DO), AL21.2 (DI)
unnamed: AL21.5 (BO), AL22.1 (BI)
unnamed: AL21.4 (DO), AL22.2 (DI)
unnamed: AL22.5 (BO), AL23.1 (BI)
unnamed: AL22.4 (DO), AL23.2 (DI)
unnamed: BUZZER3.1 (+), R42.2
unnamed: BUZZER3.2 (-), Q5.3 (C)
unnamed: D1.2, R2.2
unnamed: D10.2, R19.2
unnamed: D12.1, R25.1
unnamed: J1.A5 (CC1), R3.1
unnamed: J1.B5 (CC2), R4.1
unnamed: J2.A5 (CC1), R5.1
unnamed: J2.B5 (CC2), R6.1
unnamed: LED1.1 (-), R21.1
unnamed: LED1.2 (-), R22.1
unnamed: LED1.3 (-), R20.1
unnamed: P2.10 (A), R18.2
unnamed: Q1.1 (B), R13.2
unnamed: Q1.3 (C), R15.1
unnamed: Q1.2 (E), R14.1, U3.24 (RTS)
unnamed: Q2.1 (B), R14.2
unnamed: Q2.3 (C), R16.1
unnamed: Q2.2 (E), R13.1, U3.28 (DTR)
unnamed: D11.1, Power1.1, Q3.2 (S)
unnamed: R42.1, RV1.2
unnamed: R27.1, R28.1, SW4.4 (D)
unnamed: R29.1, R30.1, SW5.4 (D)
unnamed: R31.1, R32.1, SW6.4 (D)
unnamed: R33.1, R34.1, SW7.4 (D)
unnamed: R35.1, R36.1, SW8.4 (D)
unnamed: R37.1, R38.1, SW9.4 (D)
unnamed: R1.2, U1.3 (3V3)
unnamed: R9.1, U3.9 (RSTb)
unnamed: R12.1, U3.25 (RXD)
unnamed: R10.1, U3.11 (SUSPENDb)
unnamed: R11.1, U3.26 (TXD)
unnamed: C8.1, R7.2, R8.1, U3.8 (VBUS)
unnamed: R25.2, U4.7 (CHRG#)
unnamed: R26.1, U4.2 (PROG)
unnamed: L1.1, U5.1 (L1)
unnamed: L1.2, U5.10 (L2)
unnamed: C28.2, U5.6 (VAUX)
unnamed: C25.2, U18.2 (BYP)

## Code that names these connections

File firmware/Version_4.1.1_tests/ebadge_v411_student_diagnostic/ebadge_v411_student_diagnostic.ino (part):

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    3
  );

  printAt(10, 150, "Watch GPIO6 status LED and RGB LED.");
  printAt(10, 168, "Sequence repeats automatically.");
}

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void drawPixelStatus() {
  tft.fillRect(0, 40, 320, 160, ST77XX_BLACK);

  printAt(10, 48, "GPIO7 / 24 SK6805 LEDs", ST77XX_WHITE, 2);
  printAt(10, 92, pixelPhaseName(pixelPhase), ST77XX_YELLOW, 2);

  if (pixelPhase == PIXEL_WALK) {
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
  printAt(8, 40, "SPI3 pin test via SD card", ST77XX_WHITE, 2);

  printAt(8, 72, "CLK  GPIO38");
  printAt(8, 88, "MISO GPIO37");
  printAt(8, 104, "MOSI GPIO39");
  printAt(8, 120, "CS   GPIO40");

  printAt(
    150,
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
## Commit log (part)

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2025-04-10 Create LICENSE-HARDWARE
2025-04-10 Create LICENSE-CODE
2025-04-10 Create LICENSE-DOCS
2025-04-10 Update LICENSE-DOCS
2025-04-10 Update LICENSE-CODE
2025-04-10 Update LICENSE-HARDWARE
2025-04-10 Create minibadge-links
2025-05-14 Allow PDFs under the docs directory only (reference schematics)
2025-05-14 Add ESP32-S3-DevkitC reference schematic
2025-05-15 Add bare kicad project, lcsc part library using easyeda2kicad
2025-05-15 Stop ignoring 3D models (not cached)
2025-05-16 Fetch more LCSC parts
2025-05-16 Start feature requirement list
2025-05-16 Feature requirement list additions
2025-05-16 Alternate schematic reference
2025-05-16 KiCad library updates
2025-05-16 Update board requirements
2025-05-16 Add missing part 3D models
2025-05-16 Trim library Take advantage of existing libraries https://github.com/CDFER/JLCPCB-Kicad-Library
2025-05-16 Add ESD diodes to part library
2025-05-16 Marginal kicad schematic update
2025-05-17 Add diode from ESP devkit schematic
2025-05-17 Finish USB sub-schematic
2025-05-17 Put lcsc-lib in it's own path, some 3D model tweaks
2025-05-18 Finish linear regulator, start uart interface
2025-05-21 Finish USB-UART subcircuit
2025-05-21 Schematic on par with basic devkit
2025-05-21 Fix spelling error
2025-05-22 More generic library path
2025-05-22 add display block
2025-05-23 Add I2C GPIO expander to library
2025-06-03 Create Pinout.md
    Table for reference/updating when adding parts
2025-06-05 Moved Pinpoutmd to docs, updated Feature set
2025-06-06 Add S3-MINI-1 to library
2025-06-06 Add empty sub schematics
2025-06-06 More reference schematics and datasheets
2025-06-06 Make progress on charger, switch out some diodes
2025-06-06 Add some gamepad generic stuff
2025-06-10 Update Pinout.md
    Moved over to s3-Mini
2025-06-10 add new linear regulator that works with battery
2025-06-10 Finish charging circuit Switched out schottky diodes Better linear regulator
2025-06-13 Updated SD card sub schematic
2025-06-13 Incremental root schematic change
2025-06-13 Add tri-color LED to library
2025-06-13 Updated SPI SD card Interface
2025-06-14 Push Buttons and Single Color LED
2025-06-16 Handmade drivers, builds and uploads but does not work.
2025-06-16 Led and joystick firmware builds and uploads but nothing works (starting to suspect something else is wrong on the hardware level or my IDE rather then just poor code.)
2025-06-16 LED blink Code (not working somthing wrong with ide flash)
2025-09-25 Changed screen test to use hardware SPI
2026-02-26 added v4.0 hardware
2026-02-26 fixed labeling on 5V pin
2026-02-26 added 470R resistor to boot switch to prevent conflict
2026-03-25 started changes for 4.0.1
    fixed footprint, joystick collision, Changed to Forced PWM mode for boost converter, Fixed some silkscreen errors
2026-03-25 added remainder of changes
2026-03-25 finalized changes to v4.0.1
2026-03-25 fixed silkscreen error
    fixed silkscreen error, produced gerber files and allowed gerber zip to pass through gitignore.
2026-05-09 Fix Lynn Watson's email address in README
    Updated Lynn Watson's email address in the contributors list.
2026-06-30 added DRD, 3.3V switching reg, and VIN
2026-06-30 break before make circuit
